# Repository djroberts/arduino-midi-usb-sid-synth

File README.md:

# arduino-midi-usb-sid-synth
arduino-midi-usb-sid-synth

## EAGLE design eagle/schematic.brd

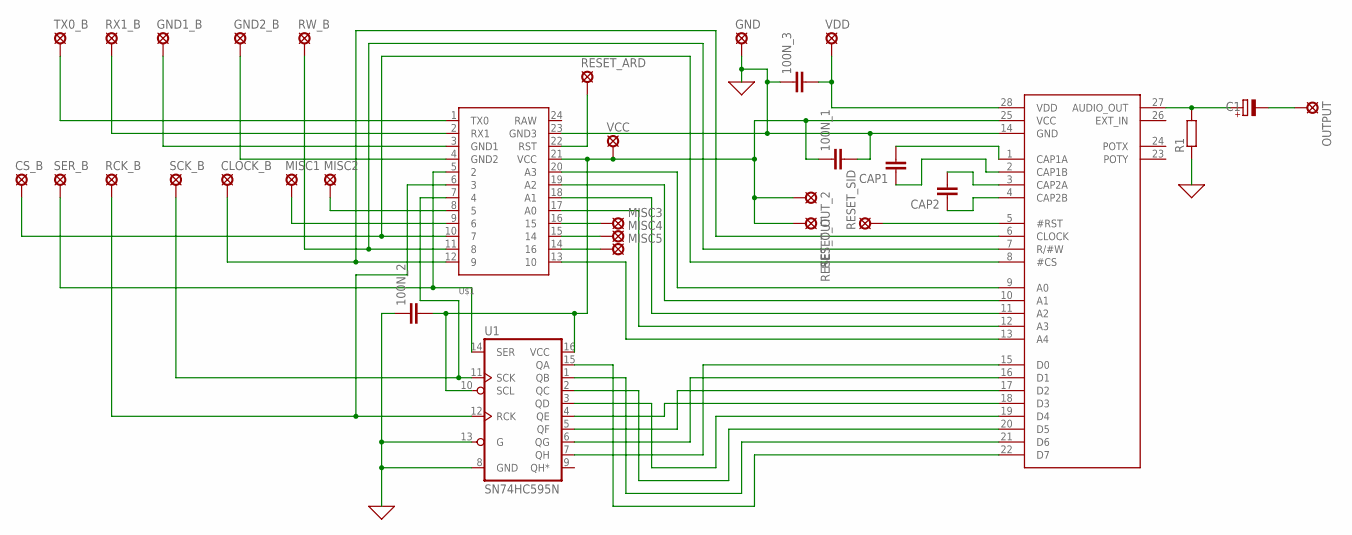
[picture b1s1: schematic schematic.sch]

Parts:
100N_1: C-EU025-025X050; C025-025X050
100N_2, 100N_3: C-EU050-025X075; C050-025X075
C1: CPOL-EUE2.5-5; E2,5-5
CAP1, CAP2: C-EU050-025X075; C050-025X075
CLOCK_B: LSP11
CS_B: LSP11
GND, GND1_B, GND2_B: LSP11
MISC1, MISC2, MISC3, MISC4, MISC5: LSP11
OUTPUT: LSP11
R1: R-EU_0204/7; 0204/7
RCK_B: LSP11
RESET_ARD: LSP11
RESET_OUT: LSP11
RESET_OUT_2: LSP11
RESET_SID: LSP11
RW_B: LSP11
RX1_B: LSP11
SCK_B: LSP11
SER_B: LSP11
TX0_B: LSP11
U1: SN74HC595N; DIP16
U$1: ARDUINOPROMICRO1; PROMICRO
U$2: SID_6581; DIL28-6
VCC: LSP11
VDD: LSP11

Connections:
0: 100N_1.2, 100N_2.1, 100N_3.1, GND.MP, R1.1, U1.8 (GND), U1.13 (G), U$1.23 (GND3), U$2.14 (GND)
unnamed: U$1.13 (10), U$2.13 (A4)
unnamed: U$1.17 (A0), U$2.12 (A3)
unnamed: U$1.18 (A1), U$2.11 (A2)
unnamed: U$1.19 (A2), U$2.10 (A1)
unnamed: U$1.20 (A3), U$2.9 (A0)
unnamed: U1.7 (QH), U$2.15 (D0)
unnamed: U1.6 (QG), U$2.16 (D1)
unnamed: U1.5 (QF), U$2.17 (D2)
unnamed: U1.4 (QE), U$2.18 (D3)
unnamed: U1.3 (QD), U$2.19 (D4)
unnamed: U1.2 (QC), U$2.20 (D5)
unnamed: U1.1 (QB), U$2.21 (D6)
unnamed: U1.15 (QA), U$2.22 (D7)
unnamed: CS_B.MP, U$1.10 (7), U$2.8 (#CS)
unnamed: RW_B.MP, U$1.11 (8), U$2.7 (R/#W)
unnamed: CLOCK_B.MP, U$1.12 (9), U$2.6 (CLOCK)
unnamed: C1.+, R1.2, U$2.27 (AUDIO_OUT)
unnamed: 100N_3.2, U$2.28 (VDD), VDD.MP
unnamed: 100N_1.1, 100N_2.2, RESET_OUT.MP, RESET_OUT_2.MP, U1.10 (SCL), U1.16 (VCC), U$1.21 (VCC), U$2.25 (VCC), VCC.MP
unnamed: CAP2.1, U$2.4 (CAP2B)
unnamed: RESET_SID.MP, U$2.5 (#RST)
unnamed: C1.-, OUTPUT.MP
unnamed: CAP2.2, U$2.3 (CAP2A)
unnamed: CAP1.2, U$2.1 (CAP1A)
unnamed: CAP1.1, U$2.2 (CAP1B)
unnamed: SER_B.MP, U1.14 (SER), U$1.5 (2)
unnamed: SCK_B.MP, U1.11 (SCK), U$1.7 (4)
unnamed: RCK_B.MP, U1.12 (RCK), U$1.6 (3)
unnamed: MISC2.MP, U$1.8 (5)
unnamed: MISC1.MP, U$1.9 (6)
unnamed: RESET_ARD.MP, U$1.22 (RST)
unnamed: MISC3.MP, U$1.16 (15)
unnamed: MISC4.MP, U$1.15 (14)
unnamed: MISC5.MP, U$1.14 (16)
unnamed: TX0_B.MP, U$1.1 (TX0)
unnamed: RX1_B.MP, U$1.2 (RX1)
unnamed: GND1_B.MP, U$1.3 (GND1)
unnamed: GND2_B.MP, U$1.4 (GND2)

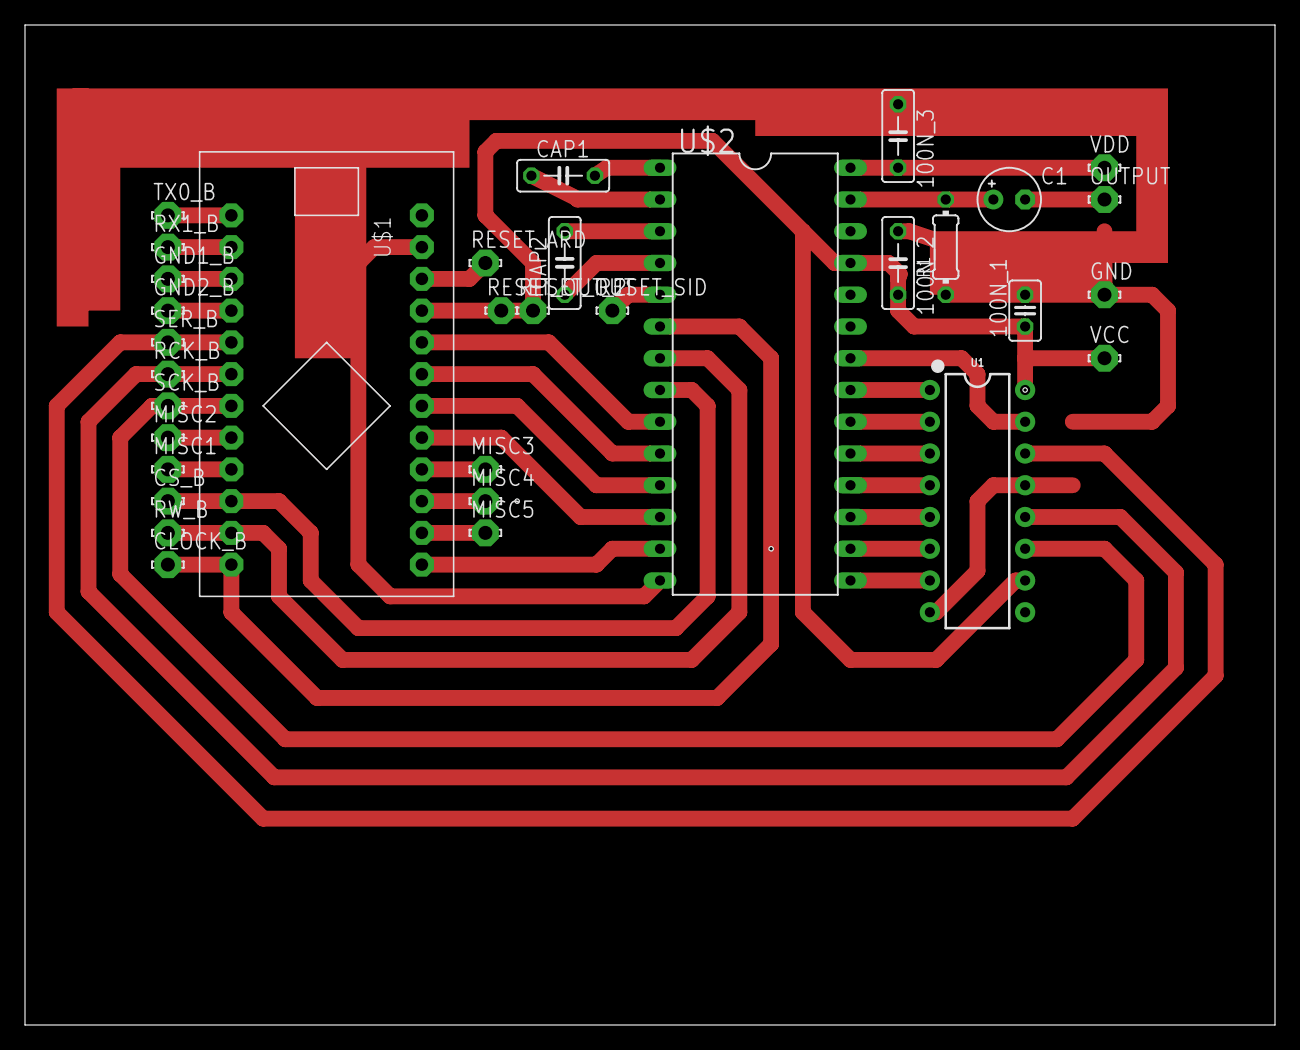
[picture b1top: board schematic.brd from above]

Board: 2 copper layers, 100.0 x 80.0 mm, 33 parts (0 on the bottom side), 39 nets.

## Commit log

2023-02-15 Added initial eagle files
2023-02-27 PCB update
2023-03-11 Synth updates
2023-03-11 Added voltage modular files
2023-03-12 Updates synth and VM modules
2023-03-12 Moved VM to root
2023-03-12 Added voice 2 and 3
2023-03-19 Adding arp

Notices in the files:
parts and their libraries:
SparkFun-IC-Logic: Licensing: Creative Commons ShareAlike 4.0 International - https://creativecommons.org/licenses/by-sa/4.0
